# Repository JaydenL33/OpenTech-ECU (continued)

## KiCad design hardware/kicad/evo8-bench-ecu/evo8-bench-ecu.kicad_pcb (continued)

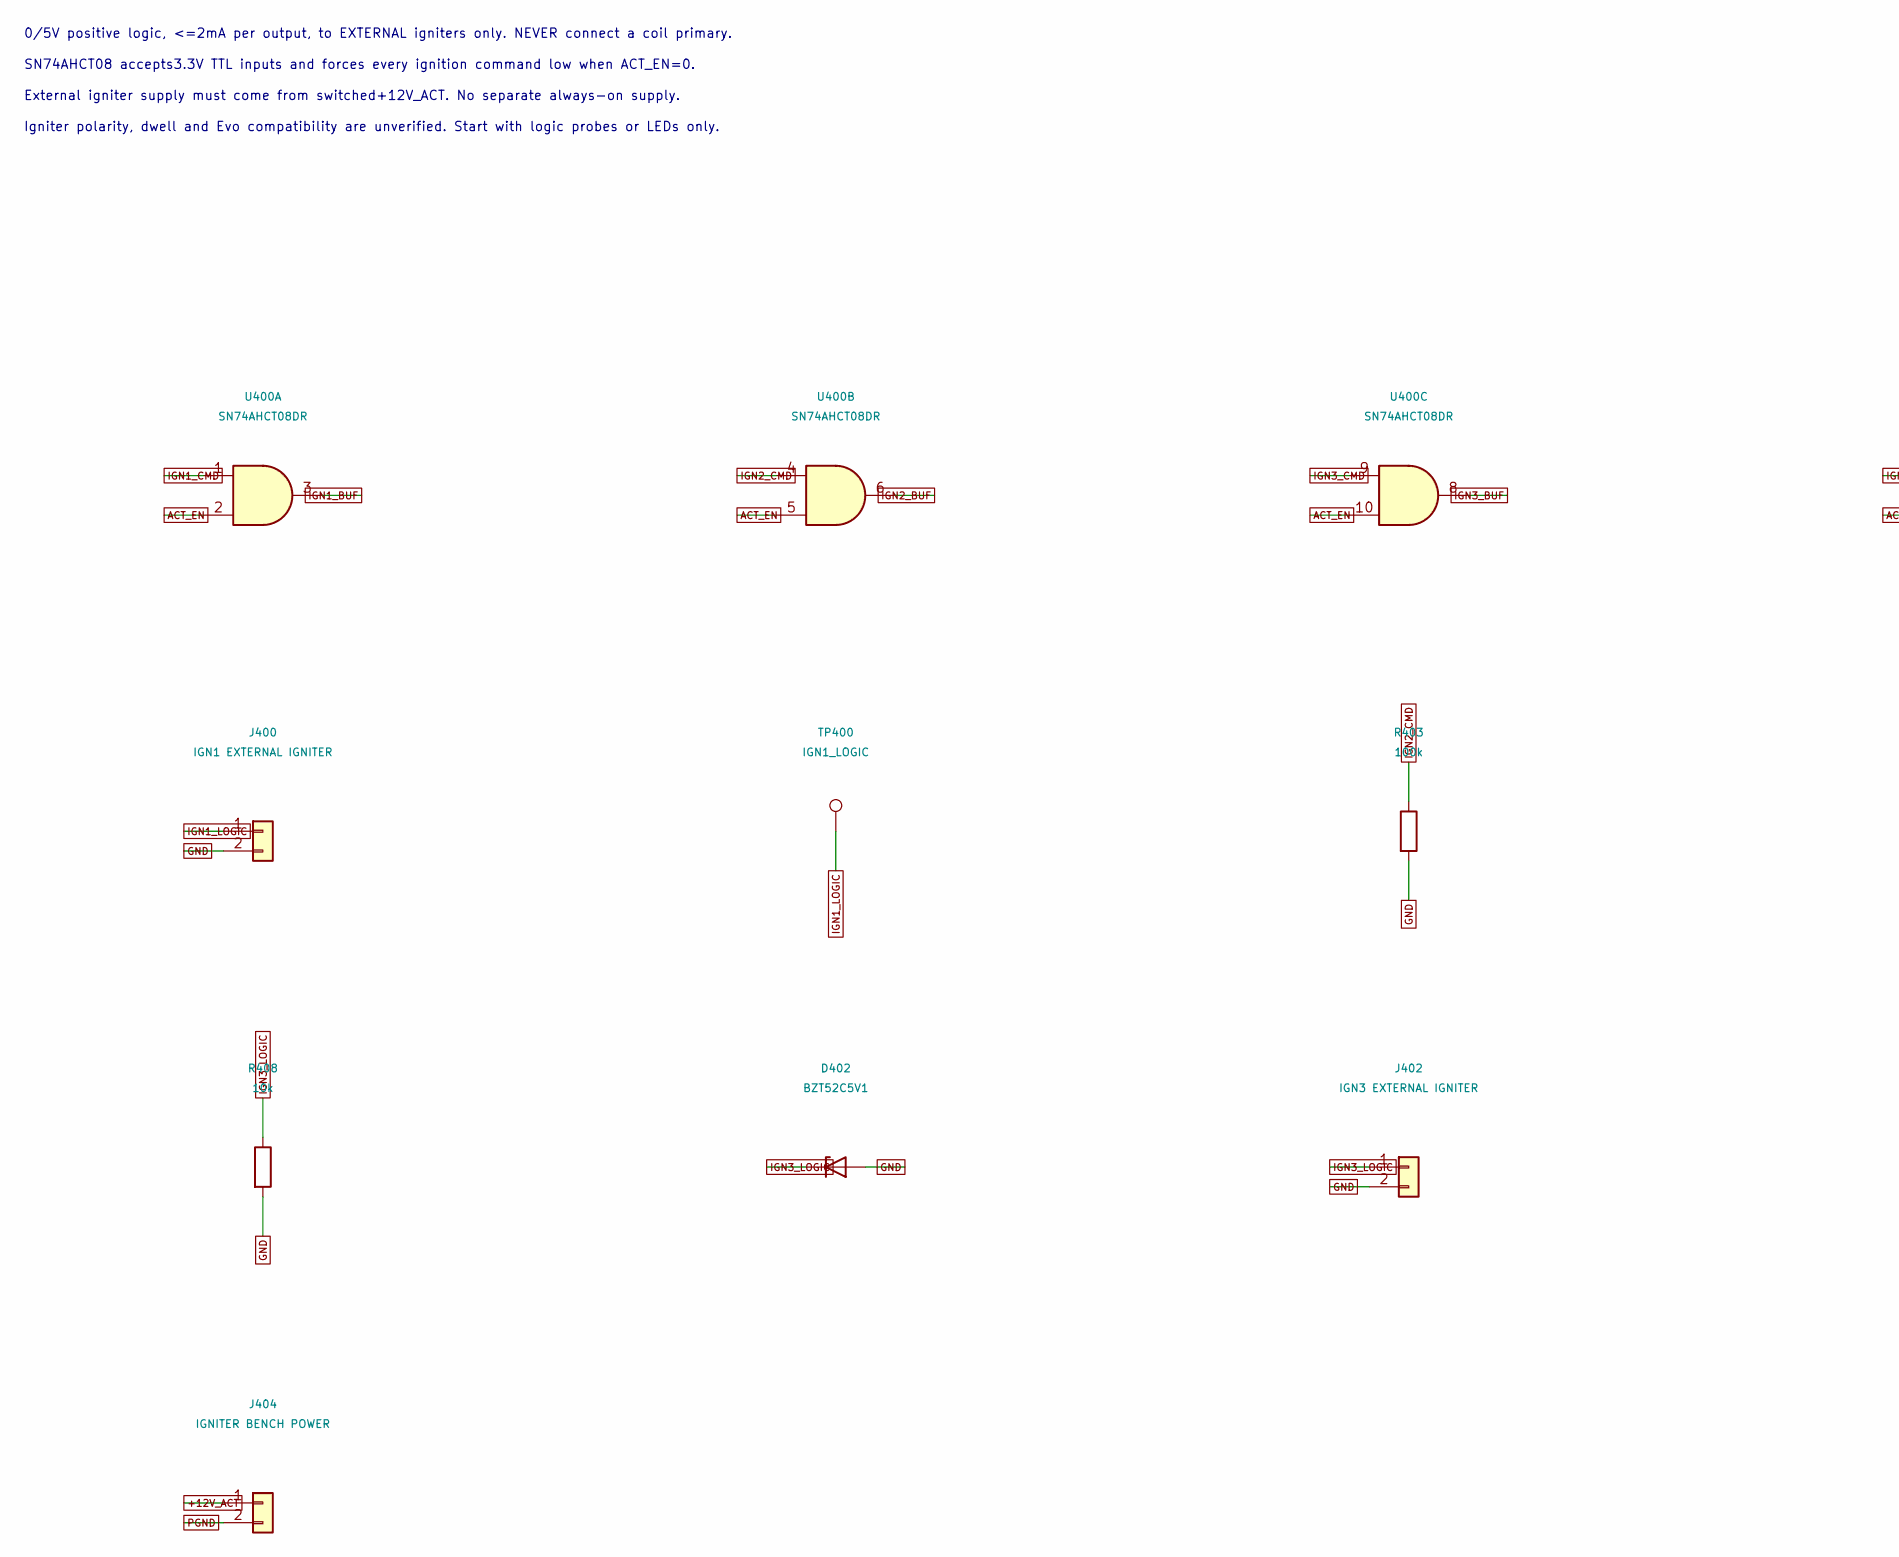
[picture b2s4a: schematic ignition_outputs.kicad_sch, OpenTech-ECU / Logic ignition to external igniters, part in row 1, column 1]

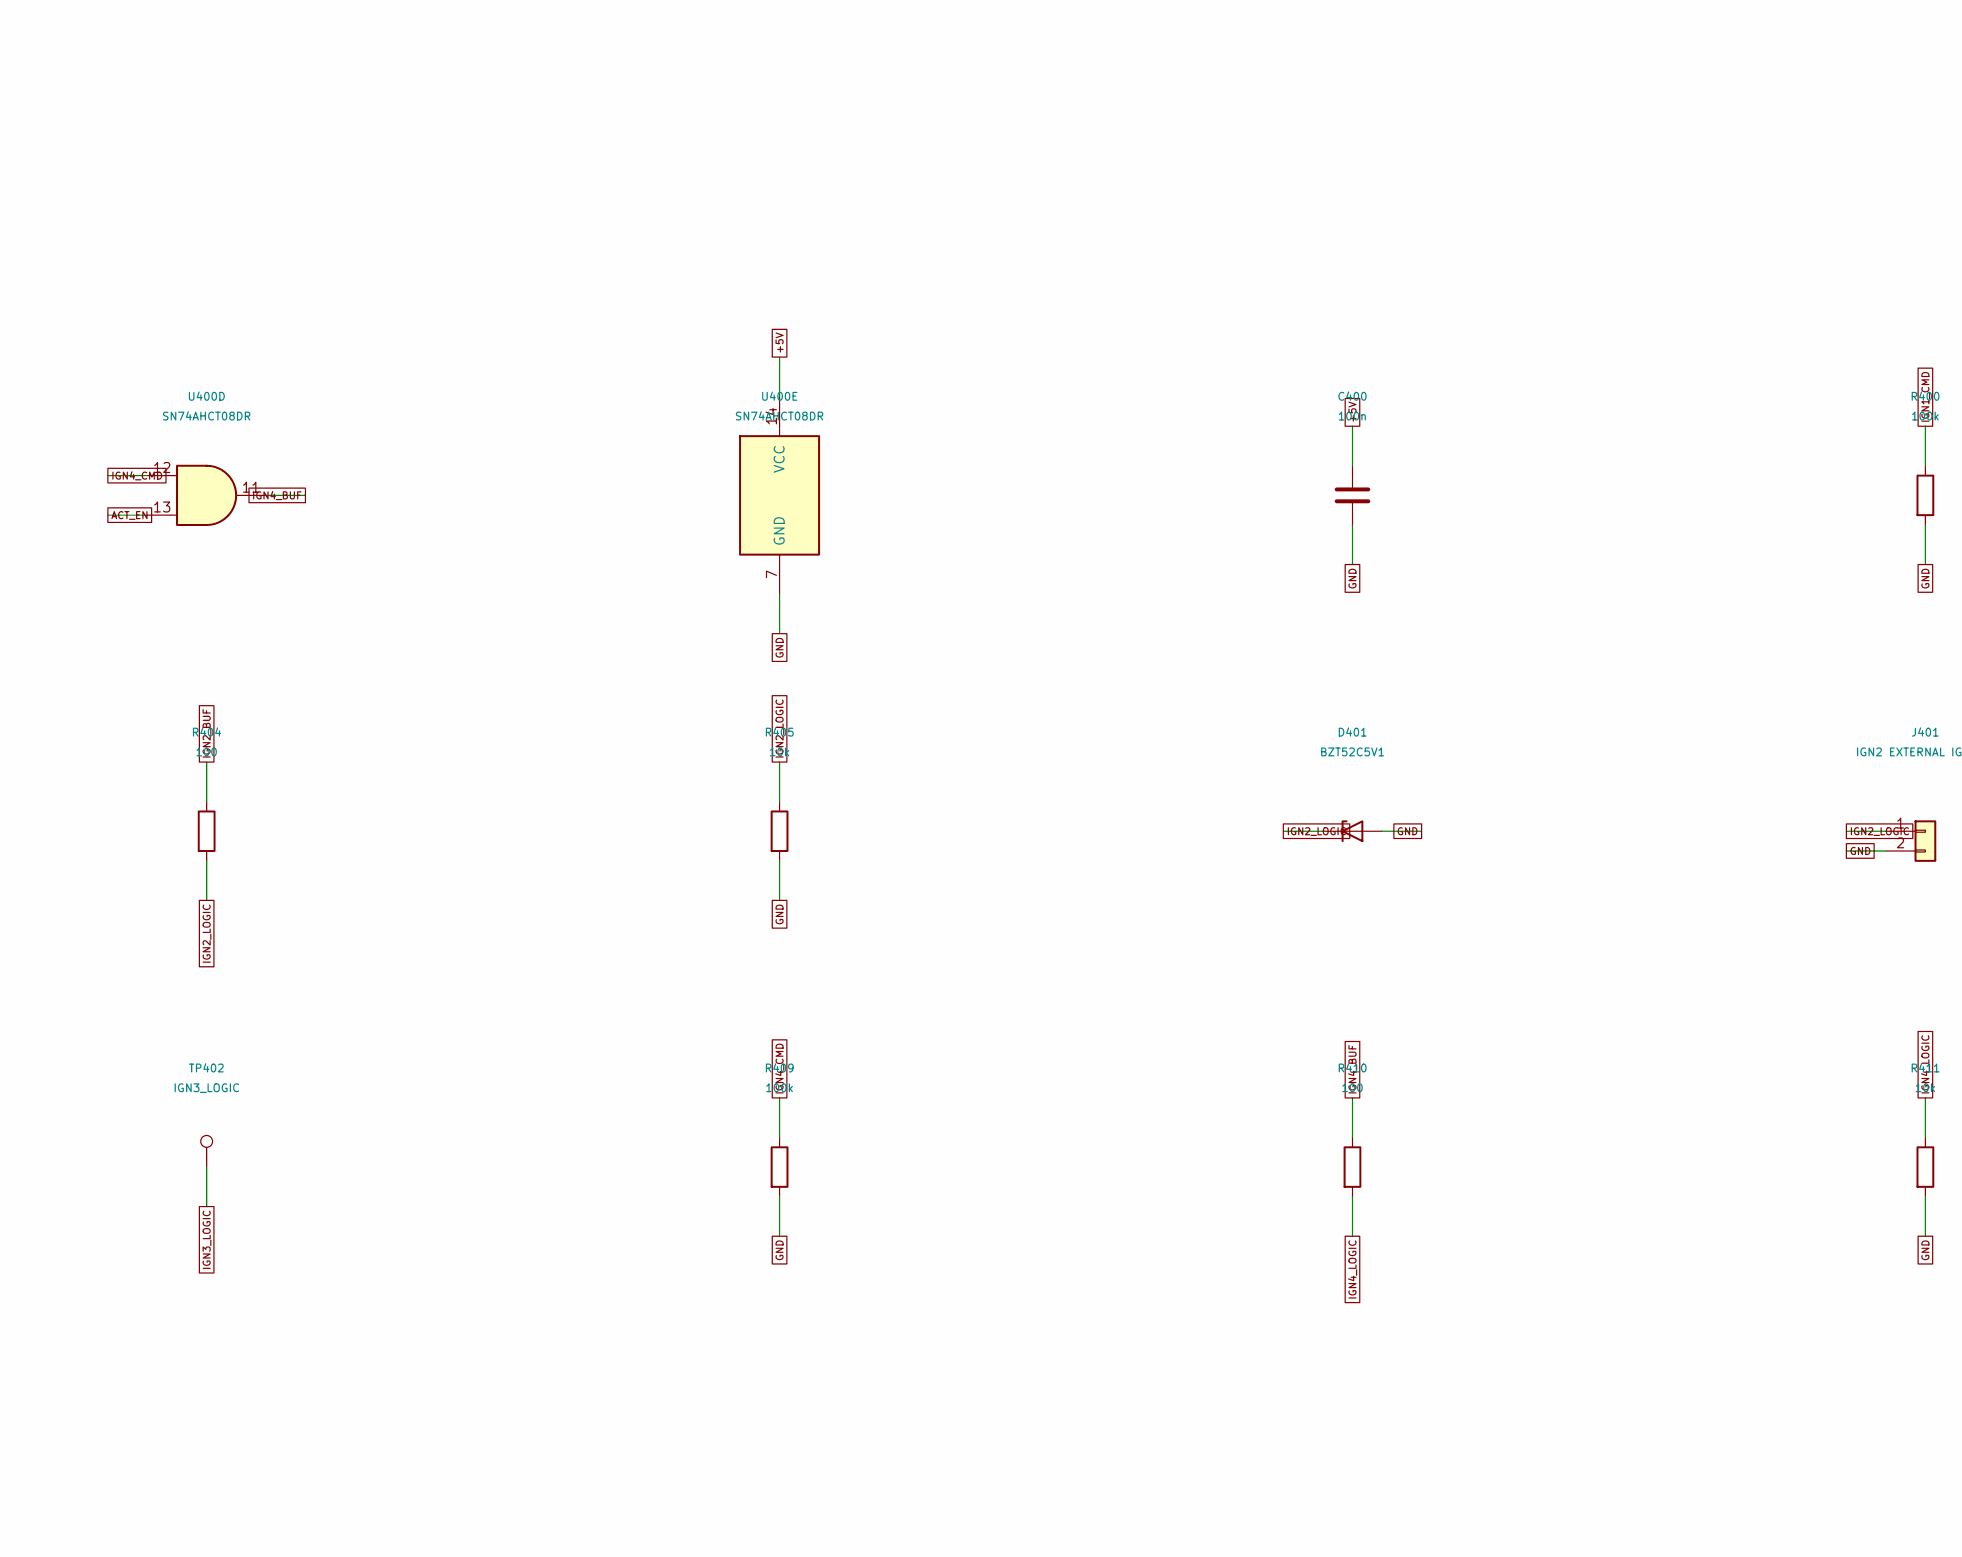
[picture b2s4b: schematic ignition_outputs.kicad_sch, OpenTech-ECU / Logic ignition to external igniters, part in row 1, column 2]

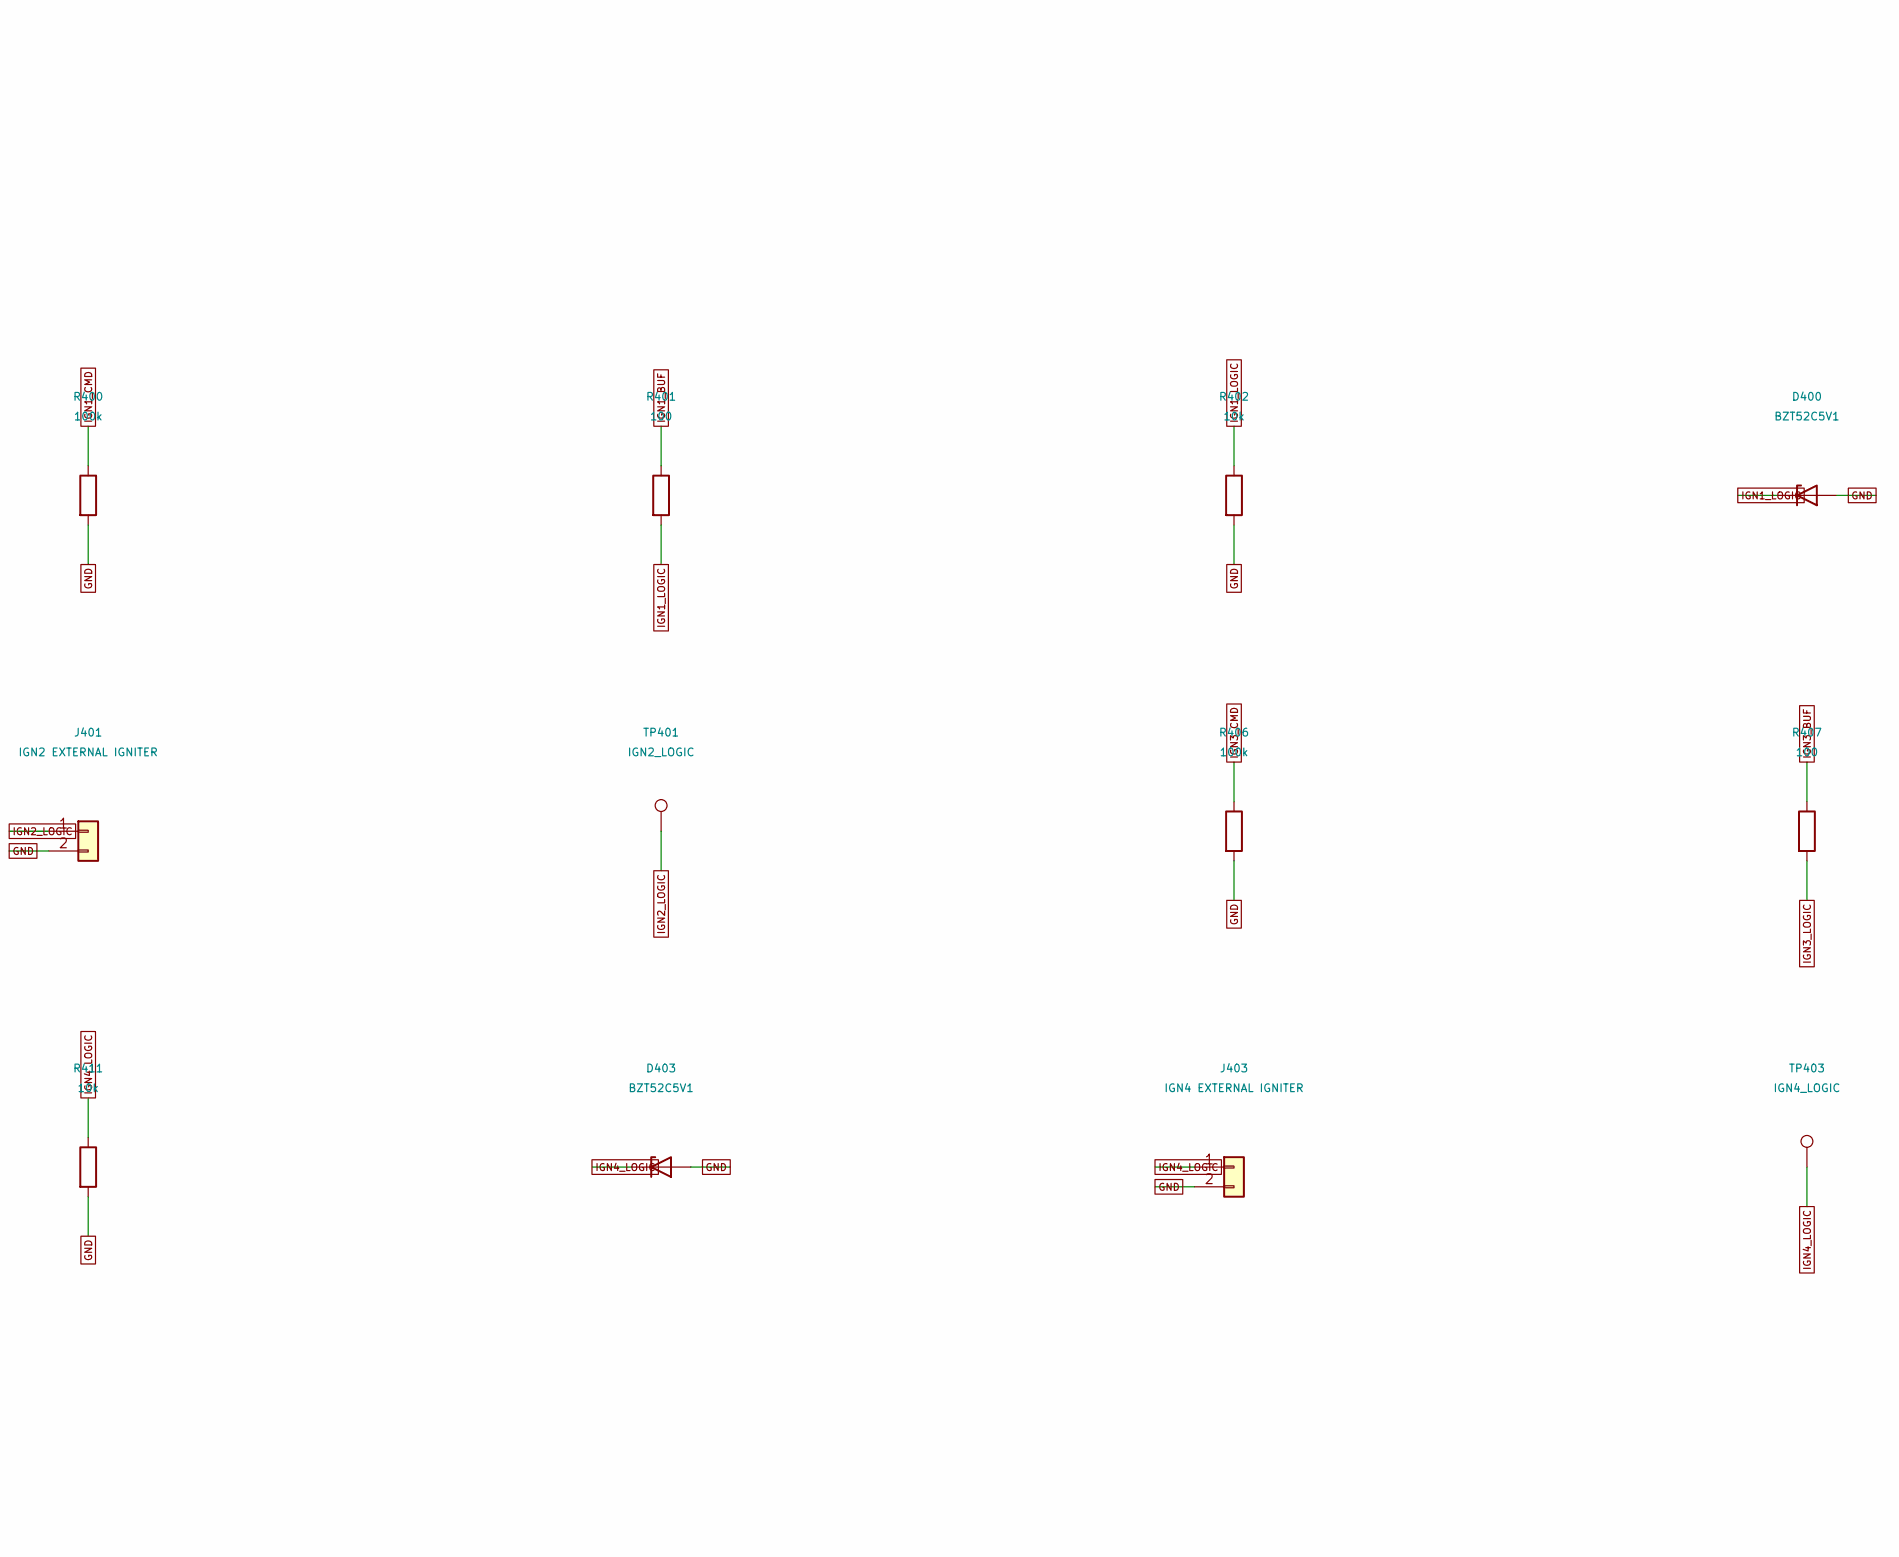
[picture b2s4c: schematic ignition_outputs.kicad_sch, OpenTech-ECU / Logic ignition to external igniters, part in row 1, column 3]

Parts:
C400: 100n; C_0805_2012Metric; MPN GRM21BR71H104KA01L
D400, D401, D402, D403: BZT52C5V1; D_SOD-123; MPN BZT52C5V1-7-F
J400: IGN1 EXTERNAL IGNITER; TerminalBlock_Phoenix_MKDS-1,5-2-5.08_1x02_P5.08mm_Horizont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; MPN 1715721
J401: IGN2 EXTERNAL IGNITER; TerminalBlock_Phoenix_MKDS-1,5-2-5.08_1x02_P5.08mm_Horizont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; MPN 1715721
J402: IGN3 EXTERNAL IGNITER; TerminalBlock_Phoenix_MKDS-1,5-2-5.08_1x02_P5.08mm_Horizont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; MPN 1715721
J403: IGN4 EXTERNAL IGNITER; TerminalBlock_Phoenix_MKDS-1,5-2-5.08_1x02_P5.08mm_Horizont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; MPN 1715721
J404: IGNITER BENCH POWER; TerminalBlock_Phoenix_MKDS-1,5-2-5.08_1x02_P5.08mm_Horizont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; MPN 1715721
R400, R403, R406, R409: 100k; R_0805_2012Metric; MPN RC0805FR-07100KL
R401, R404, R407, R410: 100; R_0805_2012Metric; MPN RC0805FR-07100RL
R402, R405, R408, R411: 10k; R_0805_2012Metric; MPN RC0805FR-0710KL
TP400: IGN1_LOGIC; TestPoint_THTPad_D2.0mm_Drill1.0mm; MPN 5010
TP401: IGN2_LOGIC; TestPoint_THTPad_D2.0mm_Drill1.0mm; MPN 5010
TP402: IGN3_LOGIC; TestPoint_THTPad_D2.0mm_Drill1.0mm; MPN 5010
TP403: IGN4_LOGIC; TestPoint_THTPad_D2.0mm_Drill1.0mm; MPN 5010
U400: SN74AHCT08DR; SOIC-14_3.9x8.7mm_P1.27mm; MPN SN74AHCT08DR

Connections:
+5V: C400.1, U400.14 (VCC); also elsewhere on the board
+12V_ACT: J404.1; also elsewhere on the board
ACT_EN: U400.2, U400.5, U400.10, U400.13; also elsewhere on the board
GND: C400.2, D400.2 (A), D401.2 (A), D402.2 (A), D403.2 (A), J400.2, J401.2, J402.2, J403.2, R400.2, R402.2, R403.2, R405.2, R406.2, R408.2, R409.2, R411.2, U400.7 (GND); also elsewhere on the board
IGN1_BUF: R401.1, U400.3
IGN1_CMD: R400.1, U400.1; also elsewhere on the board
IGN1_LOGIC: D400.1 (K), J400.1, R401.2, R402.1, TP400.1
IGN2_BUF: R404.1, U400.6
IGN2_CMD: R403.1, U400.4; also elsewhere on the board
IGN2_LOGIC: D401.1 (K), J401.1, R404.2, R405.1, TP401.1
IGN3_BUF: R407.1, U400.8
IGN3_CMD: R406.1, U400.9; also elsewhere on the board
IGN3_LOGIC: D402.1 (K), J402.1, R407.2, R408.1, TP402.1
IGN4_BUF: R410.1, U400.11
IGN4_CMD: R409.1, U400.12; also elsewhere on the board
IGN4_LOGIC: D403.1 (K), J403.1, R410.2, R411.1, TP403.1
PGND: J404.2; also elsewhere on the board

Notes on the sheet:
0/5V positive logic, <=2mA per output, to EXTERNAL igniters only. NEVER connect a coil primary.
SN74AHCT08 accepts3.3V TTL inputs and forces every ignition command low when ACT_EN=0.
External igniter supply must come from switched+12V_ACT. No separate always-on supply.
Igniter polarity, dwell and Evo compatibility are unverified. Start with logic probes or LEDs only.
